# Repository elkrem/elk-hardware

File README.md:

# Elk Board Schematics and Board files #

## Overview ##

This repository contains the schematics and board files for [Elk](https://www.kickstarter.com/projects/233173198/elk-the-dev-board-for-the-decentralized-world) board.

## Status ##

The Elk board project has been [cancelled](https://www.kickstarter.com/projects/233173198/elk-the-dev-board-for-the-decentralized-world/posts/2613884), thus the repo is unmaintained and provided for reference only in the hope it will useful.

There board in the [Kickstarter Video](https://www.kickstarter.com/projects/233173198/elk-the-dev-board-for-the-decentralized-world) is available in this [tag](https://github.com/elkrem/elk-hardware/releases/tag/v1). Other commits has been added after that.

## License and Copyright ##

These files are free; you can redistribute them and/or modify them under the terms of the Creative Commons Attribution-ShareAlike 4.0 International License only, as published by the Creative Commons organization.

These files are distributed in the hope that they will be useful, but WITHOUT ANY WARRANTY; without even the implied warranty of MERCHANTABILITY or FITNESS FOR A PARTICULAR PURPOSE.  See the Creative Commons Attribution-ShareAlike 4.0 International License for more details (a copy is included in the LICENSE file that accompanied these files).

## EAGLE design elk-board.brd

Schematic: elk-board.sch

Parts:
ANT1: AMCA31-2R450G-S1F-T3; ANTC3216X140N
C1, C3, C4, C7, C10, C11, C12, C13, C24, C26, C28, C29, C30, C31, C33, C35, C36, C37, C38, C46, C47, C48, C51, C52, C54, C55, C58, C61, C68, C70, C74, C75, C77, C78, C79, C80, C82, C83, C85, C86, C89, C90, C92, C95, C98, C99, C102, C104, C107, C108: 100nF; 0402
C2, C6, C8, C9, C19, C20, C21, C23, C57, C62, C67, C69, C76, C81, C84: 1uF; 0402
C5, C16, C25, C34, C40, C41, C42, C43, C44, C45, C56, C59, C63, C64, C65, C66, C71, C72, C73, C93, C94, C96, C97, C100, C101: 10uF; 0603
C14, C15, C49, C50: 12pF; 0402
C17, C18, C105, C106: 10uF; TOLBA_0603
C22: 1.5pF; 0402
C27: CAPACITOR-(INCH)-0402; 0402
C32: 22uF; 0603
C39, C53, C60, C91: 4.7uF; 0402
C87, C88: 18pF; 0402
C103: 22pF; 0402
IC1: KLM8G1GESD-B03P; BGA153C50P14X14_1150X1300X80
IC2: ALLWINNER--H3; BGA347C65P21X21_1400X1400X118
IC3: SY6280; SOT95P285X140-5N
IC4: K4B4G1646D-BCK0; BGA96C80P9X16_1000X1330X120
IC5, IC6, IC9: RT8059GJ5; SOT94P280X100-5N
IC7: SY8089A; SOT95P285X140-5N
IC8: NCP803SN263T1G; SOT96P237X111-3N
IC10: MP2143DJ-LF-P; SOT65P280X100-8N
JP2, JP3: PINHD-1X18_2.54-S; 1X18-S
L1: DFE252010P-4R7M=P2; INDC2520X100N
L2: 3.9nH; RESC0402_L
L3, L4, L5, L6, L7: DFE252010P-2R2M=P2; INDC2520X100N
LED1, LED3: BLUE; 0603-LED
LED2: RED; 0603-LED
LED4: LTST-E263CEGBK
Q1: AO3415A; SOT95P280X125-3N
Q2: BCM856BS; SOT65P210X110-6N
Q3: 9HT10-32.768KEZF-T; 3.2X1.5
Q4: L2N7002WT1G; SOT65P220X100-3N
R1, R2, R4, R5, R7: 30K ohm; 0402
R3, R6, R15, R19, R20, R21, R22, R23, R31, R38, R40, R50, R52: 10K ohm; 0402
R8, R10, R11, R33: 100K ohm; 0402
R9: 22 ohm; 0402
R12, R13, R29, R30, R35, R47: 10K ohm / 1%; 0402
R14: 6.8K ohm; 0402
R16, R17: 2K ohm / 1%; 0402
R18: 100 ohm; 0402
R24: 10M ohm; 0402
R25, R44: 6.8K ohm / 1%; 0402
R26: 47K ohm; 0402
R27, R28, R43: 240 ohm / 1%; 0402
R32, R45, R48: 30K ohm / 1%; 0402
R34: 15K ohm / 1%; 0402
R37, R41, R42: 1.5K ohm; 0402
R39: 33 ohm; 0402
R46: 12K ohm / 1%; 0402
R49: 1K ohm; 0402
R51: 0 ohm; 0402
S1, S2: KMR231GLFS; TACTILE_SWITCH_SMD
U1: AP6212
U2: STM32F411CEU6TR; UFQFPN-48
X1: 10118192-0001LF; 10118192-0001LF(MICRO-USB-B-AMPHENOL-FCI)
Y1: 26MHz; 4-SMD-2X1.6MM
Y2: 24MHz; CRYSTAL-SMD-3.2X2.5MM-EPSON-TSX-3225
Y3: CSTCW25M0X53-R0
Z1, Z2, Z3, Z4: AVRL101A1R1NTB/NC; 0402-RES

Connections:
1.2V: C19.1, C20.1, C23.1, C26.1, C29.1, C66.1, C72.1, C78.1, IC2.F8 (EPHY_VDD), IC2.H10 (VDD_SYS0), IC2.J10 (VDD_SYS1), IC2.J11 (VDD_SYS2), IC2.J12 (VDD_SYS3), IC2.K10 (VDD_SYS4), IC2.K11 (VDD_SYS5), IC2.K12 (VDD_SYS6), IC2.L10 (VDD_SYS7), IC2.L11 (VDD_SYS8), IC2.L12 (VDD_SYS9), IC2.L13 (VDD_SYS10), IC2.L14 (VDD_SYS11), L5.2, R35.2
1.5V: C6.1, C9.1, C11.1, C12.1, C37.1, C52.1, C55.1, C56.1, C57.1, C61.1, C62.1, C63.1, C65.1, C68.1, C69.1, C71.1, C73.1, C75.1, C76.1, C77.1, C80.1, C81.1, C83.1, C84.1, C85.1, C90.1, C92.1, IC2.L16 (VCC_DRAM0), IC2.M16 (VCC_DRAM1), IC2.N16 (VCC_DRAM2), IC2.P16 (VCC_DRAM3), IC2.P17 (VCC_DRAM4), IC2.R16 (VCC_DRAM5), IC2.T12 (VCC_DRAM6), IC2.T13 (VCC_DRAM7), IC2.T14 (VCC_DRAM8), IC2.T15 (VCC_DRAM9), IC2.U11 (VCC_DRAM10), IC4.A1 (VDDQ_1), IC4.A8 (VDDQ_2), IC4.B2 (VDD_1), IC4.C1 (VDDQ_3), IC4.C9 (VDDQ_4), IC4.D2 (VDDQ_5), IC4.D9 (VDD_2), IC4.E9 (VDDQ_6), IC4.F1 (VDDQ_7), IC4.G7 (VDD_3), IC4.H2 (VDDQ_8), IC4.H9 (VDDQ_9), IC4.K2 (VDD_4), IC4.K8 (VDD_5), IC4.N1 (VDD_6), IC4.N9 (VDD_7), IC4.R1 (VDD_8), IC4.R9 (VDD_9), L4.2, R16.2, R34.2
3.3V: C1.2, C5.1, C8.1, C10.1, C13.1, C30.1, C33.1, C34.1, C35.1, C54.1, C74.1, C100.1, C101.1, C102.1, C108.1, IC1.C6 (VDD_1), IC1.E6 (VDDF_1), IC1.F5 (VDDF_2), IC1.J10 (VDDF_3), IC1.K9 (VDDF_4), IC1.M4 (VDD_2), IC1.N4 (VDD_3), IC1.P3 (VDD_4), IC1.P5 (VDD_5), IC2.G7 (EPHY_VCC), IC2.G9 (V33_TV), IC2.G10 (VDD_EFUSE), IC2.G11 (VCC_USB), IC2.G13 (VCC_IO0), IC2.G14 (VCC_IO1), IC2.G15 (VCC_IO2), IC2.H7 (VCC_PG), IC2.H13 (VCC_IO3), IC2.H14 (VCC_IO4), IC2.J6 (HVCC), IC2.J14 (VCC_IO5), IC2.J15 (VCC_PD), IC2.K6 (VCC_RTC), IC2.N3 (VCC_PLL), IC2.V3 (AVCC), IC8.3 (VCC), L6.2, LED2.A, R1.1, R2.1, R3.2, R4.1, R5.1, R6.2, R7.1, R8.1, R11.1, R22.2, R23.2, R26.1, R31.1, R33.1, R38.1, R40.1, R45.2, R50.2, R52.1, U1.9 (VBAT), U1.22 (VDDIO)
A0: JP3.1, U2.19 (PB1)
A1: JP3.2, U2.18 (PB0)
A2: JP3.3, U2.17 (PA7)
A3: JP3.4, U2.16 (PA6)
A4: JP3.5, U2.15 (PA5)
A5: JP3.6, U2.14 (PA4)
A6: JP3.7, U2.13 (PA3)
A7: JP3.8, U2.12 (PA2)
A8: JP3.9, U2.11 (PA1)
A9: JP3.10, U2.10 (PA0)
AP_RESET#: C89.1, IC2.V6 (RESET), IC8.2 (!RESET), R38.2
B0: JP2.18, U2.32 (PA11)
B1: JP2.17, U2.33 (PA12)
B2: JP2.16, U2.28 (PB15)
B3: JP2.15, U2.27 (PB14)
B4: JP2.14, U2.26 (PB13)
B5: JP2.13, U2.25 (PB12)
BOOT0: IC2.C3 (PG8/UART1_RTS/PG_EINT8), R20.1, U2.44 (BOOT0)
C0: JP2.12, U2.45 (PB8)
C1: JP2.11, U2.29 (PA8)
C2: JP2.10, U2.46 (PB9)
C3: JP2.9, U2.21 (PB10)
C4: JP2.8, U2.43 (PB7)
C5: JP2.7, U2.42 (PB6)
CPUX_VSET: IC2.A16 (PC7/NAND_RB1), Q4.1 (G), R50.1
D0: JP2.6, U2.41 (PB5)
D1: JP2.5, U2.40 (PB4)
D2: JP2.4, U2.39 (PB3)
D3: JP2.3, U2.38 (PA15)
D4: JP2.2, U2.37 (PA14)
D5: JP2.1, LED1.A, U2.34 (PA13)
EMMC_CLK: IC1.M6 (CLK), IC2.A17 (PC5/NAND_RE/SDC2_CLK)
EMMC_CMD: IC1.M5 (CMD), IC2.E16 (PC6/NAND_RB0/SDC2_CMD), R3.1
EMMC_D0: IC1.A3 (DAT0), IC2.B18 (PC8/NAND_DQ0/SDC2_D0)
EMMC_D1: IC1.A4 (DAT1), IC2.C17 (PC9/NAND_DQ1/SDC2_D1)
EMMC_D2: IC1.A5 (DAT2), IC2.D17 (PC10/NAND_DQ2/SDC2_D2)
EMMC_D3: IC1.B2 (DAT3), IC2.C18 (PC11/NAND_DQ3/SDC2_D3)
EMMC_D4: IC1.B3 (DAT4), IC2.B17 (PC12/NAND_DQ4/SDC2_D4)
EMMC_D5: IC1.B4 (DAT5), IC2.B19 (PC13/NAND_DQ5/SDC2_D5)
EMMC_D6: IC1.B5 (DAT6), IC2.F17 (PC14/NAND_DQ6/SDC2_D6)
EMMC_D7: IC1.B6 (DAT7), IC2.C19 (PC15/NAND_DQ7/SDC2_D7)
EMMC_RST: IC1.K5 (RSTN), IC2.H16 (PC16/NAND_DQS/SDC2_RST)
GND: C1.1, C2.2, C3.1, C4.2, C5.2, C6.2, C7.1, C8.2, C9.2, C10.2, C11.2, C12.2, C13.2, C14.1, C15.1, C16.2, C17.2, C18.2, C19.2, C20.2, C21.2, C22.1, C23.2, C24.2, C25.2, C26.2, C27.1, C28.2, C29.2, C30.2, C31.2, C32.2, C33.2, C34.2, C35.2, C36.1, C38.2, C39.2, C40.2, C41.2, C42.2, C43.2, C44.2, C45.2, C46.2, C47.2, C48.2, C49.2, C50.2, C51.2, C52.2, C53.2, C54.2, C55.2, C56.2, C57.2, C58.2, C59.2, C60.2, C61.2, C62.2, C63.2, C64.2, C65.2, C66.2, C67.2, C68.2, C69.2, C70.2, C71.2, C72.2, C73.2, C74.2, C75.2, C76.2, C77.2, C78.2, C79.2, C80.2, C81.2, C82.2, C83.2, C84.2, C85.2, C86.2, C87.1, C88.1, C89.2, C90.2, C91.2, C92.2, C93.2, C94.2, C95.2, C96.2, C97.2, C98.2, C99.2, C100.2, C101.2, C102.2, C104.2, C105.2, C106.2, C107.2, C108.2, IC1.A6 (VSS_1), IC1.C4 (VSS_2), IC1.E7 (VSS_3), IC1.G5 (VSS_4), IC1.H10 (VSS_5), IC1.J5 (VSS_6), IC1.K8 (VSS_7), IC1.N2 (VSS_8), IC1.N5 (VSS_9), IC1.P4 (VSS_10), IC1.P6 (VSS_11), IC2.A21 (GND0), IC2.AA1 (GND1), IC2.G8 (GND2), IC2.H8 (GND_TV), IC2.H12 (GND3), IC2.H15 (GND4), IC2.J9 (GND7), IC2.J13 (GND5), IC2.J16 (GND6), IC2.K7 (GND12), IC2.K8 (GND13), IC2.K9 (GND14), IC2.K13 (GND8), IC2.K14 (GND9), IC2.K15 (GND10), IC2.K16 (GND11), IC2.L8 (GND16), IC2.L9 (GND17), IC2.L15 (GND15), IC2.M5 (HGND), IC2.M7 (GND24), IC2.M8 (GND25), IC2.M9 (GND26), IC2.M10 (GND18), IC2.M11 (GND19), IC2.M12 (GND20), IC2.M13 (GND21), IC2.M14 (GND22), IC2.M15 (GND23), IC2.N7 (GND33), IC2.N9 (GND34), IC2.N10 (GND27), IC2.N11 (GND28), IC2.N12 (GND29), IC2.N13 (GND30), IC2.N14 (GND31), IC2.N15 (GND32), IC2.P10 (GND35), IC2.P11 (GND36), IC2.P12 (GND37), IC2.P13 (GND38), IC2.P14 (GND39), IC2.P15 (GND40), IC2.R9 (GND46), IC2.R10 (GND41), IC2.R11 (GND42), IC2.R12 (GND43), IC2.R13 (GND44), IC2.R14 (GND45), IC2.T9 (GND_CPUXFB), IC2.T11 (GND47), IC2.U3 (AGND), IC3.2 (GND), IC4.A9 (VSS_1), IC4.B1 (VSSQ_1), IC4.B3 (VSS_2), IC4.B9 (VSSQ_2), IC4.D1 (VSSQ_3), IC4.D8 (VSSQ_4), IC4.E1 (VSS_3), IC4.E2 (VSSQ_5), IC4.E8 (VSSQ_6), IC4.F9 (VSSQ_7), IC4.G1 (VSSQ_8), IC4.G8 (VSS_4), IC4.G9 (VSSQ_9), IC4.J2 (VSS_5), IC4.J8 (VSS_6), IC4.M1 (VSS_7), IC4.M9 (VSS_8), IC4.P1 (VSS_9), IC4.P9 (VSS_10), IC4.T1 (VSS_11), IC4.T9 (VSS_12), IC5.2 (GND), IC6.2 (GND), IC7.2 (GND), IC8.1 (GND), IC9.2 (GND), IC10.4 (PGND), IC10.6 (AGND), JP3.14, JP3.15, LED4.4 (VSS), Q4.2 (S), R10.1, R12.1, R13.1, R14.1, R15.1, R17.1, R20.2, R21.2, R25.1, R27.2, R28.2, R29.1, R30.1, R37.2, R41.2, R42.2, R43.1, R44.1, R46.1, S1.3, S1.4, S2.3, S2.4, U1.1 (GND1), U1.3 (GND2), U1.20 (GND3), U1.31 (GND4), U1.33 (GND5), U1.36 (GND6), U2.8 (VSSA/VREF-), U2.20 (PB2), U2.23 (VSS), U2.35 (VSS), U2.47 (VSS), U2.49 (VSS), X1.CGND1 (SGND1), X1.CGND2 (SGND2), X1.CGND3 (SGND3), X1.CGND4 (SGND4), X1.CGND5 (SGND5), X1.CGND6 (SGND6), X1.GND, Y1.2, Y1.4, Y2.2 (3), Y2.4 (3), Y3.GND, Z1.1, Z2.1, Z3.1, Z4.1
GPIOA15/SPI1_MOSI: IC2.F14 (PA15/SPI1_MOSI/UART3_RTS/PA_EINT15), R39.1
H3_UART1_RX: IC2.D3 (PG7/UART1_RX/PG_EINT7), U2.30 (PA9)
H3_UART1_TX: IC2.G4 (PG6/UART1_TX/PG_EINT6), U2.31 (PA10)
KERNEL_LED: IC2.B21 (PD6/RGMII_NULL/MII_RXERR/RMII_RXER), LED3.A
MCU_3.3V: C58.1, C59.1, C64.1, C67.1, C70.1, C79.1, C82.1, C86.1, C91.1, JP3.16, JP3.17, L3.2, R19.1, R32.2, U2.1 (VBAT), U2.9 (VDDA/VREF+), U2.24 (VDD), U2.36 (VDD), U2.48 (VDD)
MCU_REG_EN: IC2.H17 (PD1/RGMII_RXD2/MII_RXD2/RMII_NULL/DI_RX), IC5.1 (EN), R21.1
MCU_RST: C36.2, IC2.B1 (PG13/PCM1_DIN/PG_EINT13), JP3.11, R19.2, U2.7 (NRST)
unnamed: R9.1, U1.17 (SDIO_DATA_CLK)
unnamed: JP3.12, R51.2
unnamed: IC5.3 (LX), L3.1
unnamed: LED1.K, R37.1
unnamed: LED3.K, R42.1
unnamed: IC6.3 (LX), L4.1
unnamed: R10.2, U1.34 (BT_RST_N)
unnamed: IC5.5 (FB), R25.2, R32.1
unnamed: C15.2, U1.11 (XTAL_OUT), Y1.1
unnamed: C14.2, U1.10 (XTAL_IN), Y1.3
unnamed: JP3.13, R49.2
unnamed: ANT1.1 (FEED), C27.2, L2.2
unnamed: LED4.2 (DIN), R39.2
unnamed: C25.1, L1.2, U1.23 (VIN_LDO)
unnamed: U2.5 (PH0/OSC_IN), Y3.IN
unnamed: U2.6 (PH1/OSC_OUT), Y3.OUT
unnamed: L1.1, U1.21 (VIN_LDO_OUT)
unnamed: IC6.5 (FB), R29.2, R34.1
unnamed: IC7.3 (LX), L5.1
unnamed: C22.2, L2.1, U1.2 (WL_BT_ANT)
unnamed: LED2.K, R41.1
unnamed: C39.1, U2.22 (VCAP1)
unnamed: IC4.L8 (ZQ), R27.1
unnamed: C16.1, IC3.1 (OUT), Q1.3 (D), Q2.1 (EMITTER_TR1), X1.VBUS, Z4.2
unnamed: IC7.5 (FB), R30.2, R35.1
unnamed: C49.1, IC2.V5 (X32KIN), Q3.1, R24.2
unnamed: IC10.3 (SW), L7.1
unnamed: C103.2, IC10.7 (FB), R46.2, R47.1, R48.2
unnamed: IC3.3 (ISET), R14.2
unnamed: IC9.3 (LX), L6.1
unnamed: IC2.V10 (SZQ), R43.2
unnamed: IC9.5 (FB), R44.2, R45.1
unnamed: Q4.3 (D), R48.1
unnamed: Q1.1 (G), Q2.3 (COLLECTOR_TR2), R12.2
unnamed: Q2.2 (BASE_TR1), Q2.5 (BASE_TR2), Q2.6 (COLLECTOR_TR1), R13.2
unnamed: C50.1, IC2.U4 (X32KOUT), Q3.2, R24.1
unnamed: C60.1, IC2.H11 (VDD_EFUSEBP)
unnamed: IC2.AA6 (NMI), R26.2
unnamed: IC2.AA5 (KEYADC), R33.2
unnamed: IC4.L9 (NC_4), R28.1
PWR_DRAM: IC2.A14 (PA21/PCM0_DIN/SIM_VPPPP/PA_EINT21), IC6.1 (EN), R22.1
PWR_STB: IC2.A20 (PD4/RGMII_RXCK/MII_RXCK/RMII_NULL), IC7.1 (EN), IC10.8 (EN), R23.1
RESET_SW: IC2.F13 (PA8/SIM_DATA/PA_EINT8), R52.2, S2.1, S2.2
SA0: IC2.T17 (SA0), IC4.N3 (A0)
SA1: IC2.U18 (SA1), IC4.P7 (A1)
SA2: IC2.V19 (SA2), IC4.P3 (A2)
SA3: IC2.V20 (SA3), IC4.N2 (A3)
SA4: IC2.V21 (SA4), IC4.P8 (A4)
SA5: IC2.Y19 (SA5), IC4.P2 (A5)
SA6: IC2.Y20 (SA6), IC4.R8 (A6)
SA7: IC2.V15 (SA7), IC4.R2 (A7)
SA8: IC2.W18 (SA8), IC4.T8 (A8)
SA9: IC2.Y18 (SA9), IC4.R3 (A9)
SA10: IC2.P19 (SA10), IC4.L7 (A10/AP)
SA11: IC2.N19 (SA11), IC4.R7 (A11)
SA12: IC2.R18 (SA12), IC4.N7 (A12/!BC)
SA13: IC2.V12 (SA13), IC4.T3 (A13)
SA14: IC2.N17 (SA14), IC4.T7 (A14)
SA15: IC2.R17 (SA15), IC4.M7 (NC_5)
SBA0: IC2.W17 (SBA0), IC4.M2 (BA0)
SBA1: IC2.T18 (SBA1), IC4.N8 (BA1)
SBA2: IC2.V17 (SBA2), IC4.M3 (BA2)
SCAS: IC2.U15 (SCAS), IC4.K3 (!CAS)
SCKE0: IC2.AA21 (SCKE0), IC4.K9 (CKE)
SCKE1: IC2.Y21 (SCKE1), IC4.J9 (NC_2)
SCK_N: IC2.AA20 (SCKB), IC4.K7 (!CK), R18.1
SCK_P: IC2.AA19 (SCK), IC4.J7 (CK), R18.2
SCS0: IC2.W20 (SCS0), IC4.L2 (!CS)
SCS1: IC2.W21 (SCS1), IC4.L1 (NC_3)
SDC1_CLK: IC2.J3 (PG0/SDC1_CLK/PG_EINT0), R9.2
SDC1_CMD: IC2.L2 (PG1/SDC1_CMD/PG_EINT1), R7.2, U1.16 (SDIO_DATA_CMD)
SDC1_D0: IC2.H4 (PG2/SDC1_D0/PG_EINT2), R5.2, U1.18 (SDIO_DATA_0)
SDC1_D1: IC2.F3 (PG3/SDC1_D1/PG_EINT3), R4.2, U1.19 (SDIO_DATA_1)
SDC1_D2: IC2.C2 (PG4/SDC1_D2/PG_EINT4), R2.2, U1.14 (SDIO_DATA_2)
SDC1_D3: IC2.C1 (PG5/SDC1_D3/PG_EINT5), R1.2, U1.15 (SDIO_DATA_3)
SDQ0: IC2.N20 (SDQ0), IC4.F7 (DQL1)
SDQ1: IC2.P21 (SDQ1), IC4.H8 (DQL5)
SDQ2: IC2.P20 (SDQ2), IC4.F8 (DQL3)
SDQ3: IC2.U21 (SDQ3), IC4.H3 (DQL4)
SDQ4: IC2.R19 (SDQ4), IC4.H7 (DQL7)
SDQ5: IC2.T20 (SDQ5), IC4.E3 (DQL0)
SDQ6: IC2.U19 (SDQ6), IC4.G2 (DQL6)
SDQ7: IC2.U20 (SDQ7), IC4.F2 (DQL2)
SDQ8: IC2.J19 (SDQ8), IC4.A7 (DQU4)
SDQ9: IC2.H20 (SDQ9), IC4.A2 (DQU5)
SDQ10: IC2.H21 (SDQ10), IC4.A3 (DQU7)
SDQ11: IC2.J21 (SDQ11), IC4.B8 (DQU6)
SDQ12: IC2.L20 (SDQ12), IC4.C8 (DQU2)
SDQ13: IC2.L21 (SDQ13), IC4.D7 (DQU0)
SDQ14: IC2.M21 (SDQ14), IC4.C3 (DQU1)
SDQ15: IC2.M19 (SDQ15), IC4.C2 (DQU3)
SDQM0: IC2.M20 (SDQM0), IC4.E7 (DML)
SDQM1: IC2.G20 (SDQM1), IC4.D3 (DMU)
SDQS0_N: IC2.R21 (SDQSB0), IC4.G3 (!DQSL)
SDQS0_P: IC2.R20 (SDQS0), IC4.F3 (DQSL)
SDQS1_N: IC2.J20 (SDQSB1), IC4.B7 (!DQSU)
SDQS1_P: IC2.K20 (SDQS1), IC4.C7 (DQSU)
SETUP_SW: IC2.A13 (PA20/PCM0_DOUT/SIM_VPPEN/PA_EINT20), IC2.W6 (UBOOT), R40.2, S1.1, S1.2
SODT0: IC2.W11 (SODT0), IC4.K1 (ODT)
SODT1: IC2.V11 (SODT1), IC4.J1 (NC_1)
SRAS: IC2.V13 (SRAS), IC4.J3 (!RAS)
SRST: IC2.U16 (SRST), IC4.T2 (!RESET)
SVREF: C37.2, C38.1, C51.1, C104.1, IC2.T16 (SVREF), IC4.H1 (VREFDQ), IC4.M8 (VREFCA), R16.1, R17.2
SWE: IC2.W13 (SWE), IC4.L3 (!WE)
UART0_RX: IC2.H6 (PA5/UART0_RX/PWM0/PA_EINT5), R51.1
UART0_TX: IC2.F5 (PA4/UART0_TX/PA_EINT4), R49.1
USB0_DRVVBUS: IC2.B16 (PC2/NAND_CLE/SPI0_CLK), IC3.4 (EN), R15.2
USB0_N: IC2.B5 (USB_DM0), X1.D-, Z3.2
USB0_OTGID: IC2.D1 (PG12/PCM1_DOUT/PG_EINT12), R6.1, X1.ID, Z1.2
USB0_P: IC2.A5 (USB_DP0), X1.D+, Z2.2
VDDI_EMMC: C3.2, C7.2, IC1.C2 (VDDI)
VDD_CPUFB: C103.1, IC2.T10 (VDD_CPUXFB), R47.2
VDD_CPUS: C2.1, C4.1, C53.1, IC2.J7 (VDD_CPUS0), IC2.J8 (VDD_CPUS1), IC2.M4 (RTC_VIO)
VDD_CPUX: C17.1, C18.1, C21.1, C24.1, C28.1, C31.1, C105.1, C106.1, C107.1, IC2.N8 (VDD_CPUX0), IC2.P6 (VDD_CPUX1), IC2.P7 (VDD_CPUX2), IC2.P8 (VDD_CPUX3), IC2.P9 (VDD_CPUX4), IC2.R6 (VDD_CPUX5), IC2.R7 (VDD_CPUX6), IC2.R8 (VDD_CPUX7), IC2.T6 (VDD_CPUX8), IC2.T7 (VDD_CPUX9), IC2.T8 (VDD_CPUX10), IC2.U6 (VDD_CPUX11), IC2.U9 (VDD_CPUX12), IC10.5 (OUT), L7.2
VIN: C32.1, C40.1, C41.1, C42.1, C43.1, C44.1, C45.1, C46.1, C47.1, C48.1, C93.1, C94.1, C95.1, C96.1, C97.1, C98.1, C99.1, IC3.5 (IN), IC5.4 (VIN), IC6.4 (VIN), IC7.4 (IN), IC9.1 (EN), IC9.4 (VIN), IC10.2 (VIN), JP3.18, LED4.1 (VDD), Q1.2 (S), Q2.4 (EMITTER_TR2)
WIFI_32K: IC2.P3 (X32KFOUT), R31.2, U1.24 (LPO)
WL_REG_ON: IC2.T3 (PL7/S_JTAG_SI/S_PL_EINT7), R11.2, U1.12 (WL_REG_ON)
WL_WAKE_HOST: IC2.M3 (PG10/PCM1_SYNC/PG_EINT10), R8.2, U1.13 (WL_HOST_WAKE)
X24_IN: C87.2, IC2.K2 (X24MIN), Y2.3 (2)
X24_OUT: C88.2, IC2.K1 (X24MOUT), Y2.1

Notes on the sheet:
WiFi Module - AP6212
DDR3 RAM
MCU Voltage Regulator 3.3V /1A
Decoupling Capacitors
VDDA & VSSA Pin 8 & 9
VDD & VSS
User LED
User Microcontroller
Pin Headers
USB Connector
DRAM 1.5V/1A
VDD-SYS 1.2V/2A
VCC-CPUX 1.1V/3A
VCC-IO 3.3V/1A
Microprocessor Interfaces
MCU_USART1_TX
MCU_USART1_RX
USER RGB LED
SETUP Switch
Kernel LED
Power LED
PWR-STB
PWR-DRAM
PWRON/WORK
STANDBY
PWROFF
MODE
STATE
RESET Switch
Boot1
MPU Decoupling Capacitors
GPIOL6/CPUX-VSET = 0, VDD-CPUX=1.1V GPIOL6/CPUX-VSET = 1, VDD-CPUX=1.3V
Bottom Side Caps
Diff100
Diff100 - 25 mils - Clock-200 : Clock
CPUX
3.3V
1.2V
1.5V

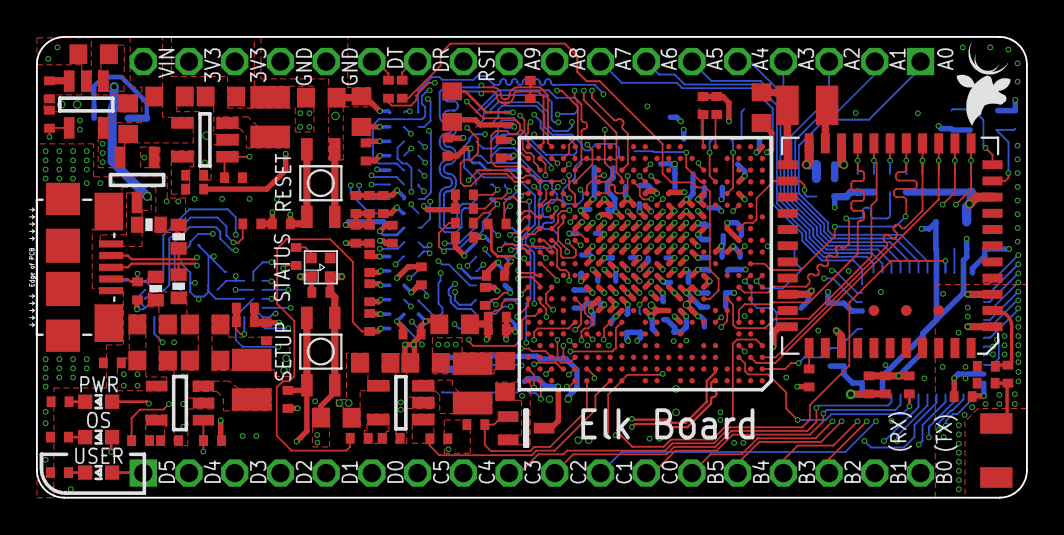
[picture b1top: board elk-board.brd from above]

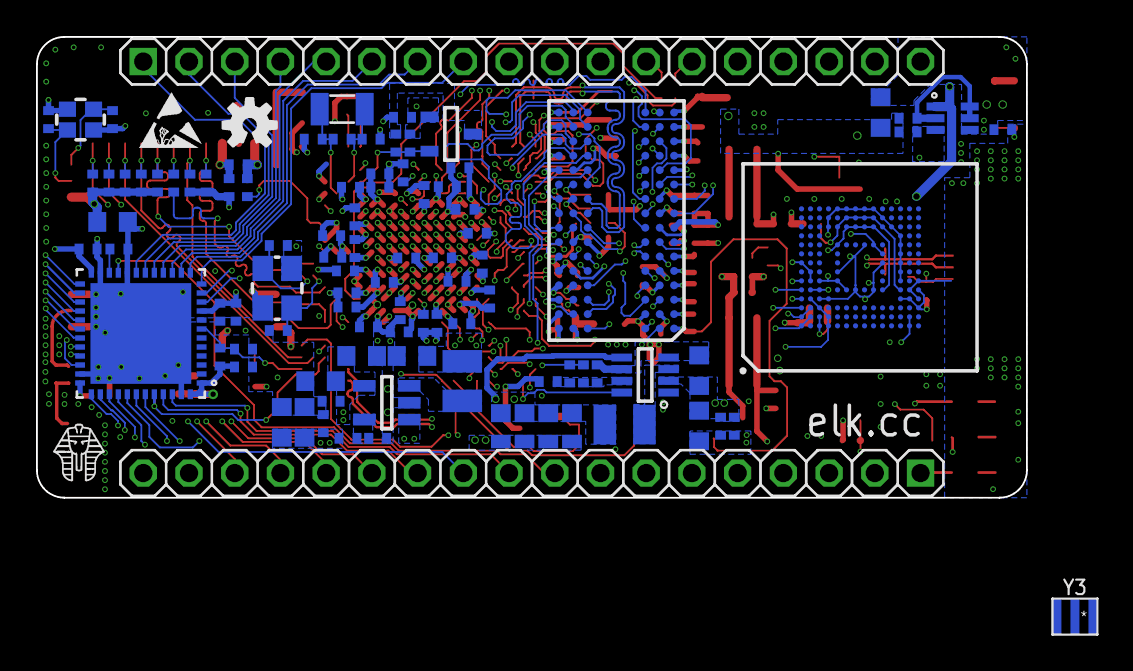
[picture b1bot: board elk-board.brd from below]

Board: 8 copper layers, 55.0 x 25.6 mm, 200 parts (98 on the bottom side), 173 nets.

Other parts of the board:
U$1: OSHW-LOGO-S

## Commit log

2019-07-08 Initial commit
    1st iteration (H3) sent to China on June, 12th, 2019
2019-09-04 Added pdf schematics
2019-09-04 Finished eMMC Data Lines legth matching (CMD is not included)
2019-09-04 Added and Modified GND vias and increased eMMC CLK length and it's clearance with nearby traces
2019-09-04 Moved the Antenna a little bit
2019-09-04 Added TX & RX Silkscreen
2019-09-04 Added emmc chip and integrated antenna
2019-09-04 Modified DR & DT positions (a Mistake from 1st Iteration)
2019-09-04 Added Some GND vias and moved USB_DRVVBUS via position
2019-09-04 Modified the GND & PWR Planes around the Antenna
2019-09-04 CONNECT UBOOT WITH SETUP Button
2019-09-04 Did UBOOT Push Button layout
2019-09-04 Finished emmc and antenna (WIP)
2019-09-04 Changed the RAM part Number in the schematic and modified the Wifi module label
2019-09-04 Decrease LEDs brightness + MCU_REG_ON (Pull Down)
2019-09-04 90ohm Impedence Control Enhancment
    USB Differenctial Pair
2019-09-04 RAM Clock Impedance Control
2019-09-04 Modified USB Diff Pair Impedence and Length Matching
2019-09-04 Added External Oscillator to MCU Schematics
2019-09-04 Added schematics pdf
2019-09-04 Added license and readme files

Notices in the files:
parts and their libraries:
crystal-geyer_V1_0: Copyright: Geyer-Electronic
SparkFun: Licensing: CC v3.0 Share-Alike You are welcome to use this library for commercial purposes.
SparkFun-Clocks: Licensing: Creative Commons ShareAlike 4.0 International - https://creativecommons.org/licenses/by-sa/4.0
